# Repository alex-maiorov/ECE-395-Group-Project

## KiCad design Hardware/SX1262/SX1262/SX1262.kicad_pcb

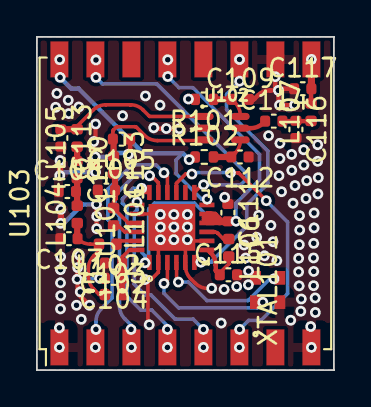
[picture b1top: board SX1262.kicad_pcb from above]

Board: 2 copper layers, 16.5 x 18.5 mm, 30 parts (1 on the bottom side), 28 nets.

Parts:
C101, C102, C103, C104, C105, C107, C108, C109, C110, C111, C112, C113, C114, C115, C116, C117: C_Small; C_0402_1005Metric
L101, L102, L103, L104, L105, L106, L107: L_Small; L_0402_1005Metric
R101, R102: R_Small_US; R_0402_1005Metric
U101: SX1262IMLTRT; QFN50P400X400X100-25N
U102: PE4259; SOT65P215X110-6N
U103, U104: RFM69HCW; HOPERF_RFM9XW_SMD
XTAL101: NX2016SA-32M-EXS00A-CS06465; NX2016SA_NDK-L

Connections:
/PLZ: C117.2, L107.2, U103.9 (ANT), U104.8 (GND)
/RF0: L102.1, U101.23 (RFO)
/RFI_N: L101.2, U101.22 (RFI_N)
/RFI_P: C101.2, C103.2, L101.1, U101.21 (RFI_P)
/SX1262_DIO1: U101.13 (DIO1), U103.15 (DIO1), U104.2 (MISO)
/SX1262_DIO2: R102.1, U101.12 (DIO2), U103.16 (DIO2), U104.1 (GND)
/SX1262_DIO3: U101.6 (DIO3), U103.11 (DIO3), U104.6 (RESET)
/SX1262_MISO: U101.16 (MISO), U103.2 (MISO), U104.15 (DIO1)
/SX1262_MOSI: U101.17 (MOSI), U103.3 (MOSI), U104.14 (DIO0)
/SX1262_NSS: U101.19 (NSS), U103.5 (NSS), U104.12 (DIO4)
/SX1262_RESET: U101.15 (~NRESET), U103.6 (RESET), U104.11 (DIO3)
/SX1262_SCK: U101.18 (SCK), U103.4 (SCK), U104.13 (3.3V)
/VDD_RADIO: C111.2, U101.1 (VDD_IN), U101.10 (VBAT), U101.11 (VBAT_IO), U103.13 (3.3V), U104.4 (SCK)
/VR_PA: C102.1, C104.1, L103.2, U101.24 (VR_PA)
GND: C101.1, C102.2, C104.2, C105.1, C107.2, C108.1, C109.2, C111.1, C112.1, C113.2, C115.2, C116.2, C117.1, U101.2 (GND), U101.5 (GND), U101.8 (GND), U101.20 (GND), U101.25 (EXP), U102.2 (GND), U103.1 (GND), U103.8 (GND), U103.10 (GND), U104.7 (DIO5), U104.9 (ANT), U104.16 (DIO2), XTAL101.2, XTAL101.4
unnamed: C103.1, C105.2, U102.3 (RF2)
unnamed: C107.1, L102.2, L103.1, L104.1
unnamed: C108.2, C110.2, L104.2
unnamed: C109.1, R101.1, U102.6 (~CTRL/~{VDD)
unnamed: C110.1, L105.1
unnamed: C112.2, R102.2, U102.4 (CTRL)
unnamed: C113.1, L105.2, U102.1 (RF1)
unnamed: C114.1, U102.5 (RFC)
unnamed: C114.2, C116.1, L107.1
unnamed: C115.1, L106.2, U101.7 (VREG)
unnamed: L106.1, U101.9 (DCC_SW)
unnamed: U101.3 (XTA), XTAL101.1
unnamed: U101.4 (XTB), XTAL101.3

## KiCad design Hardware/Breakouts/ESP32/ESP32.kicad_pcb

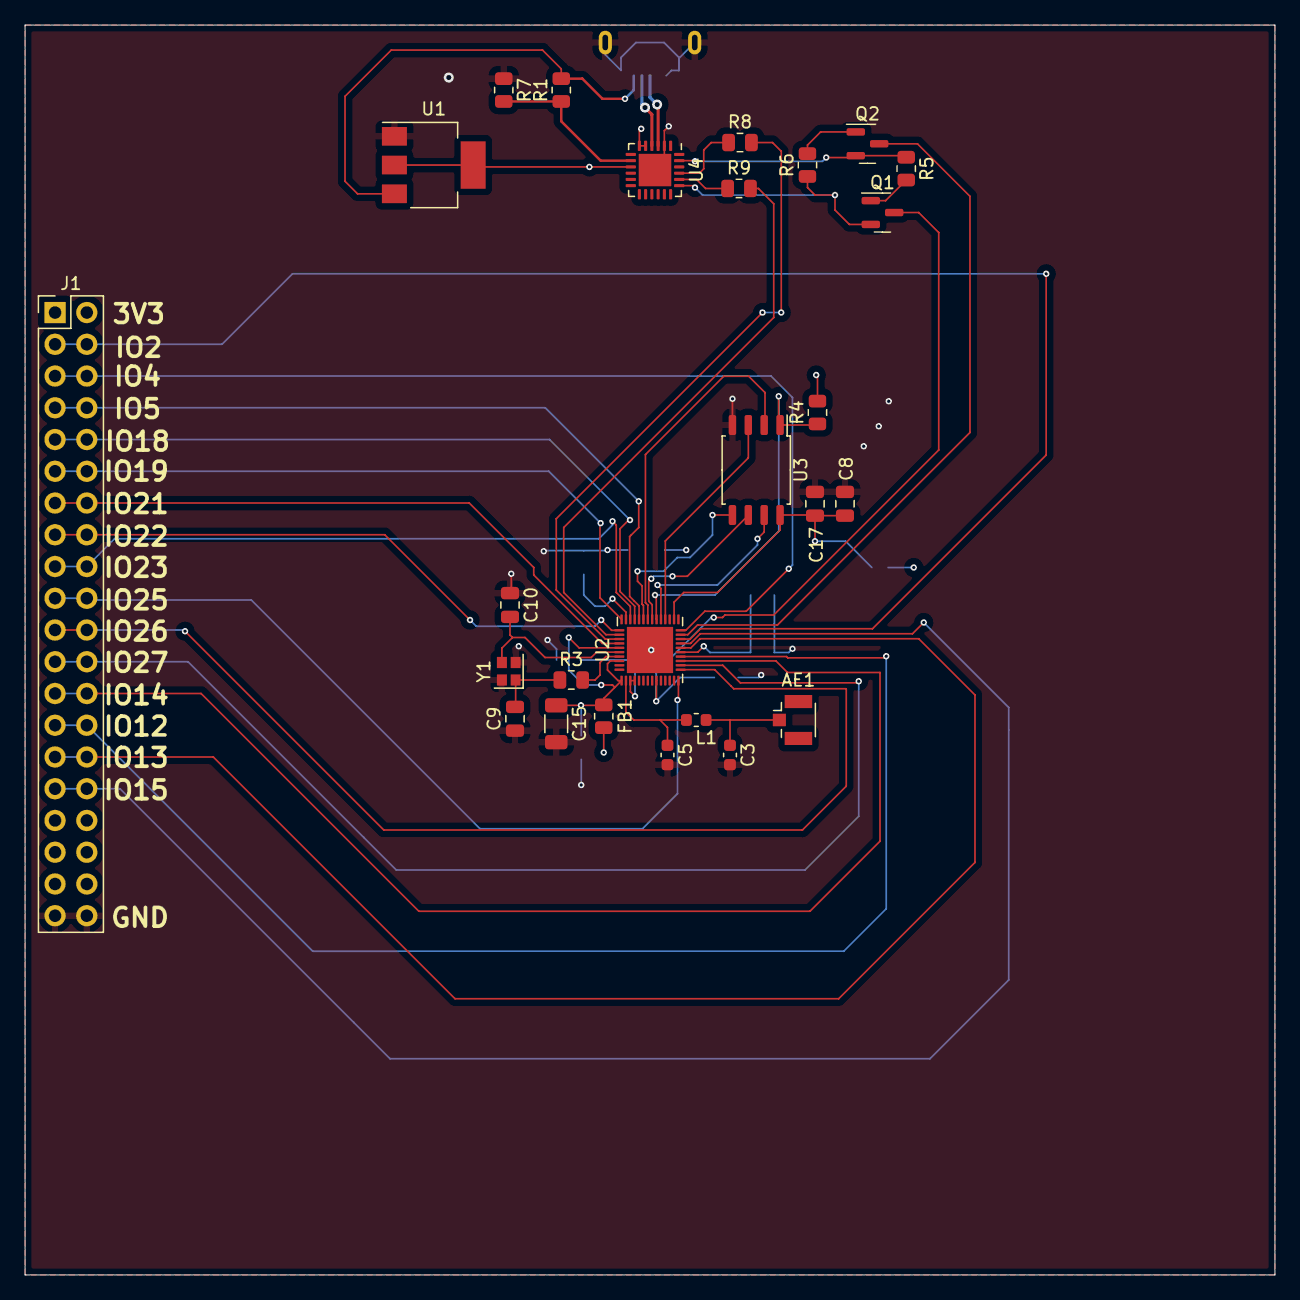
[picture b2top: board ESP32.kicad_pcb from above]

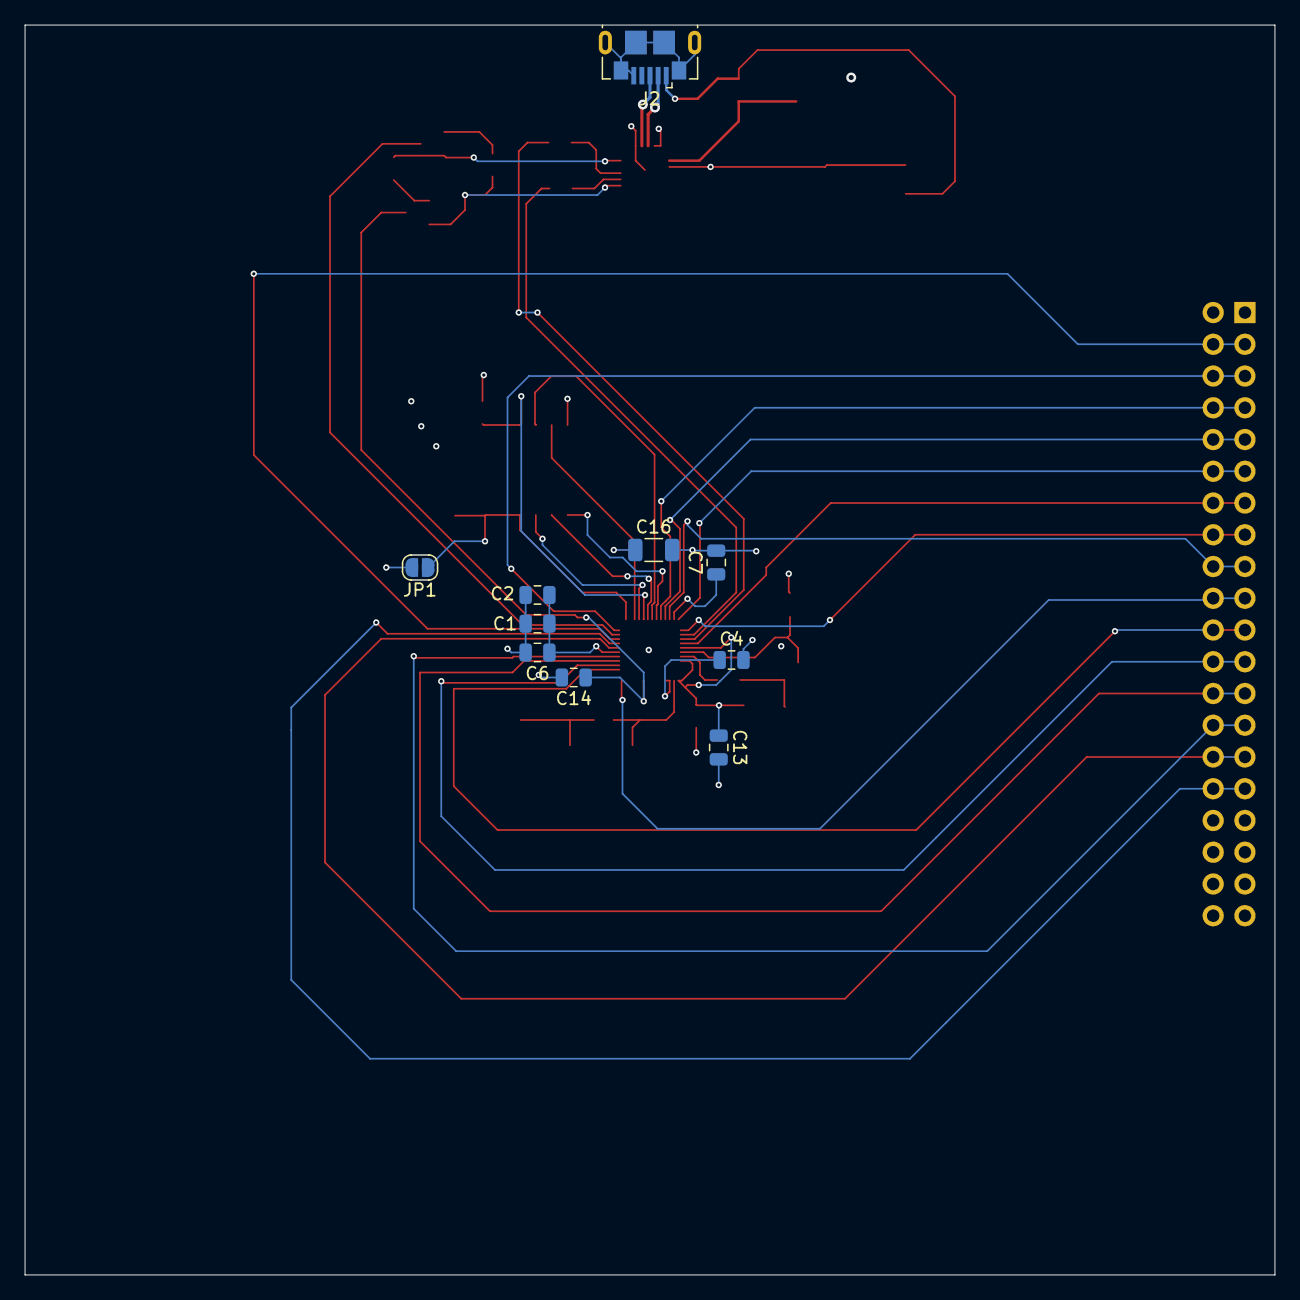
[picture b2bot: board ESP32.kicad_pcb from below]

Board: 4 copper layers, 100.0 x 100.0 mm, 36 parts (10 on the bottom side), 44 nets.

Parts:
AE1: Antenna; U.FL_Hirose_U.FL-R-SMT-1_Vertical
C1, C2, C4, C6, C7, C8, C13, C17: 100n; C_0805_2012Metric
C3, C5: C; C_0603_1608Metric
C9: 8p; C_0805_2012Metric
C10: C; C_0805_2012Metric
C14: 1u; C_0805_2012Metric
C15, C16: 10u; C_1206_3216Metric
FB1: FerriteBead; R_0805_2012Metric
J1: Conn_02x20_Odd_Even; PinHeader_2x20_P2.54mm_Vertical
J2: USB_B_Micro; USB_Micro-B_GCT_USB3076-30-A
JP1: Jumper_2_Open; SolderJumper-2_P1.3mm_Open_RoundedPad1.0x1.5mm
L1: 0.6n; L_0603_1608Metric
Q1, Q2: BC817; SOT-23
R1: 22.1k; R_0805_2012Metric
R3: 1k; R_0805_2012Metric
R4, R5, R6, R7, R8, R9: 10k; R_0805_2012Metric
U1: AMS1117-3.3; SOT-223-3_TabPin2
U2: ESP32; QFN-48-1EP_5x5mm_P0.35mm_EP3.7x3.7mm
U3: W25Q128JVS; SOIC-8_5.23x5.23mm_P1.27mm
U4: CP2102N-Axx-xQFN24; QFN-24-1EP_4x4mm_P0.5mm_EP2.6x2.6mm
Y1: Crystal_GND24; Crystal_SMD_2016-4Pin_2.0x1.6mm

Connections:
+3V3: C1.1, C2.1, C4.1, C6.1, C7.1, C16.1, FB1.1, J1.1, J1.2, JP1.2 (B), R4.2, U1.2 (VO), U2.3 (VDD3P3), U2.4 (VDD3P3), U2.19 (VDD3P3_RTC), U2.37 (VDD3P3_CPU), U4.5 (VIO), U4.6 (VDD), U4.9 (~RST)
/DTR: Q2.2 (E), R5.1, U4.23 (~DTR)
/EN: C14.1, Q1.3 (C), U2.9 (CHIP_PU)
/FLASH_CLK: U2.31 (SD_CLK/GPIO6), U3.6 (CLK)
/FLASH_CS: R4.1, U2.30 (SD_CMD/GPIO11), U3.1 (~CS)
/FLASH_IO0: U2.33 (SD_DATA_1/GPIO8), U3.5 (DI(IO0))
/FLASH_IO1: U2.32 (SD_DATA_0/GPIO7), U3.2 (DO(IO1))
/FLASH_IO2: U2.28 (SD_DATA_2/GPIO9), U3.3 (IO2)
/FLASH_IO3: U2.29 (SD_DATA_3/GPIO10), U3.7 (IO3)
/IO0: Q2.3 (C), U2.23 (GPIO0/BOOT/ADC2_CH1)
/IO2: J1.3, J1.4, U2.22 (GPIO2/ADC2_CH2)
/IO4: J1.5, J1.6, U2.24 (GPIO4/ADC2_CH0)
/IO5: J1.7, J1.8, U2.34 (GPIO5)
/IO12: J1.27, J1.28, U2.18 (MTDI/GPIO12/ADC2_CH5)
/IO13: J1.29, J1.30, U2.20 (MTCK/GPIO13/ADC2_CH4)
/IO14: J1.25, J1.26, U2.17 (MTMS/GPIO14/ADC2_CH6)
/IO15: J1.31, J1.32, U2.21 (MTDO/GPIO15/ADC2_CH3)
/IO18: J1.9, J1.10, U2.35 (GPIO18)
/IO19: J1.11, J1.12, U2.38 (GPIO19)
/IO21: J1.13, J1.14, U2.42 (GPIO21)
/IO22: J1.15, J1.16, U2.39 (GPIO22)
/IO23: J1.17, J1.18, U2.36 (GPIO23)
/IO25: J1.19, J1.20, U2.14 (GPIO25/ADC2_CH8/DAC_1)
/IO26: J1.21, J1.22, U2.15 (GPIO26/ADC2_CH9/DAC_2)
/IO27: J1.23, J1.24, U2.16 (GPIO27/ADC2_CH7)
/RTS: Q1.2 (E), R6.1, U4.19 (~RTS)
/RXD: R9.2, U2.40 (U0RXD/GPIO3)
/TXD: R8.2, U2.41 (U0TXD/GPIO1)
GND: C1.2, C2.2, C3.2, C4.2, C5.2, C6.2, C7.2, C8.2, C9.1, C10.1, C13.2, C14.2, C15.2, C16.2, C17.2, J1.39, J1.40, J2.5 (GND), J2.6 (Shield), R7.1, U1.1 (GND), U2.49 (GND), U3.4 (GND), U4.2 (GND), U4.25 (GND), Y1.2, Y1.4
unnamed: AE1.1 (A), C3.1, L1.1
unnamed: C5.1, L1.2, U2.2 (LNA_IN)
unnamed: C9.2, R3.1, Y1.1
unnamed: J2.2 (D-), U4.4 (D-)
unnamed: J2.3 (D+), U4.3 (D+)
unnamed: Q1.1 (B), R5.2
unnamed: Q2.1 (B), R6.2
unnamed: C13.1, C15.1, FB1.2, U2.1 (VDDA), U2.43 (VDDA), U2.46 (VDDA)
unnamed: C10.2, U2.44 (XTAL_N), Y1.3
unnamed: R3.2, U2.45 (XTAL_P)
unnamed: R1.1, R7.2, U4.8 (VBUS)
unnamed: R9.1, U4.20 (RXD)
unnamed: R8.1, U4.21 (TXD)
VBUS: J2.1 (VBUS), R1.2, U1.3 (VI)
VDD_SDIO: C8.1, C17.1, JP1.1 (A), U2.26 (VDD_SDIO), U3.8 (VCC)

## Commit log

2023-01-24 Initial commit to setup kicad project
    Initial commit to setup kicad project
2023-01-24 Created SX12xx schematic
    Created SX12xx schematic
2023-01-28 Added SX1262 Schematic + Footprint
    Added SX1262 Schematic + Footprint
2023-02-06 stuff
2023-02-06 nuked stuff
2023-02-06 added git submodule
2023-02-06 started sch
2023-02-07 stuff part 3
2023-02-21 Added mesh v1 board
2023-02-27 did schematic almost done
2023-02-28 Nearly finished sch
2023-04-25 Added Sx1262 and basic mesh code
    Added Sx1262 and basic mesh code
2023-05-01 satuff
2023-05-01 plz work
2023-05-01 Did code
2023-05-08 Added old code
